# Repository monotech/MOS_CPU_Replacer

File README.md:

# Monotech PCs - MOS CPU Replacer  
**Replace rare/expensive/unreliable MOS CPUs**  
6510 *(C64) (8500 is same as 6510)*  
6510T *(1551 floppy drive)*  
8501 *(C16, C116, Plus/4) (7501 is same as 8501)*  
8502 *(C128)*

Licensed under Creative Commons BY-SA: (https://creativecommons.org/licenses/by-sa/4.0/)

If you want one, check my store for stock: (https://monotech.fwscart.com)

The above four CPUs have the same dies I believe, with just different internal pads exposed to the DIP-40 pins.  
It's a standard 6502 die, with an added 8-bit bidirectional I/O port, tri-state bus buffers, and an AEC latch enable for 8501 mode.

This device uses a standard 6502 CPU, and implements the extra functions using discrete logic - no programmable parts.  
Standard 6502 CPUs are abundant and cheap, and produced by many manufacturers (Rockwell, UMC, Synertek, MOS, etc).

You can use a 65C02 or W65C02, but this is untested, and will cause compatibility issues with some software at the least, or not work at the worst.  
If using a WDC W65C02, you must cut jumper W.

Build instructions are on the back of the PCB. This document is for clarification if you find it unclear.

It may struggle to fit inside a C116 or Plus/4 due to height, so for these machines you should solder the 6502 directly to the module's PCB, or solder the module directly to the C116 or Plus/4 motherboard.  
For C16, height is not a problem.

It is tested to fit next to a PLA20V8 replacement in a 250407 board. Other oversized replacement boards may interfere and require installing the module in an extra socket to raise it up.

Status as of Rev1:
-

- :heavy_check_mark: 6510 config: Tested working in a C64 and C64C with a wide range of software. In one scenario, it was discovered that it causes graphical glitches when used in a C64 with a C0pperdragon video conversion device (which watches the VIC-II pins). This was on Rev1. It may or may not be resolved on Rev2.
- :heavy_check_mark: 6510T config: I don't have a 1551, but someone else has done some basic testing in their own, and it works.
- :x: 8501 config: Tested working in a C16 and a Plus/4, but it has been found that at least one program crashes on a 64K-modded C16, that doesn't crash with a real 8501.
- :x: 8502 config: Works but has graphical glitches, likely due to a timing issue, so should only be built if you plan to help me diagnose this. For 8502, you must install a 2MHz-rated CPU (such as 6502A).

Known issues:
-

- A local enthusiast has discovered that using this adapter in 8501 config in their 64K-modded C16, results in Slipstream (https://psytronik.itch.io/slipstream) hanging, and causing resets to stop working (need a power cycle). One other person has confirmed this, and confirmed it doesn't happen with a real 8501, so the issue is with the MOS CPU Replacer. I will look into possible causes and update this page if a solution is found. Testing the C64 version of Slipstream in a C64 works fine with either a real 6510 or the MOS CPU Replacer in 6510 config.
- One user reported that it causes graphical glitches when used in a C64 (6510 config) with a C0pperdragon video conversion device (which watches the VIC-II pins), but works well otherwise. This was on Rev1. It may or may not be resolved on Rev2.
- I am sometimes working on improving the device, and hopefully reaching 100% compatibility.

---

Instructions:
-

1. Solder the solder-jumpers first (red dots).
1. Solder two 20-pin round-pin headers (cyan rectangles). (Not 21-pin!)
1. Solder the DIP-40 socket (yellow rectangles).
1. Install the 6502, and test the device.
    Don't install the device backwards or misaligned!

**The example picture below is for 8501 config (Jumpers: C, Headers: E). Steps 1 and 2 are different for the other three configs.**

**Troubleshooting**

- See the Known Issues section above.
- Double-check for shorts and that you soldered the correct solder jumpers.
- Crappy single-wipe IC sockets that Commodore used, can cause a lot of headache. Replace them.
- Your 6502 from Aliexpress/eBay may be fake or faulty. Sometimes they are actually 65C02 that have been re-marked as 6502.
- Some models of 6502 may be incompatible - I haven't tested all of them.
- I haven't tested every combination of Commodore motherboard revision, PLA replacement, marginal IC, or timing-sensitive demo.

**Changelog**

- Rev 2: used an unused HCT126 gate to buffer the PHI2 output, improving compatibility. Only affects 6510 and 6510T configurations which actually have a PHI2 output.
- Rev 1: First version

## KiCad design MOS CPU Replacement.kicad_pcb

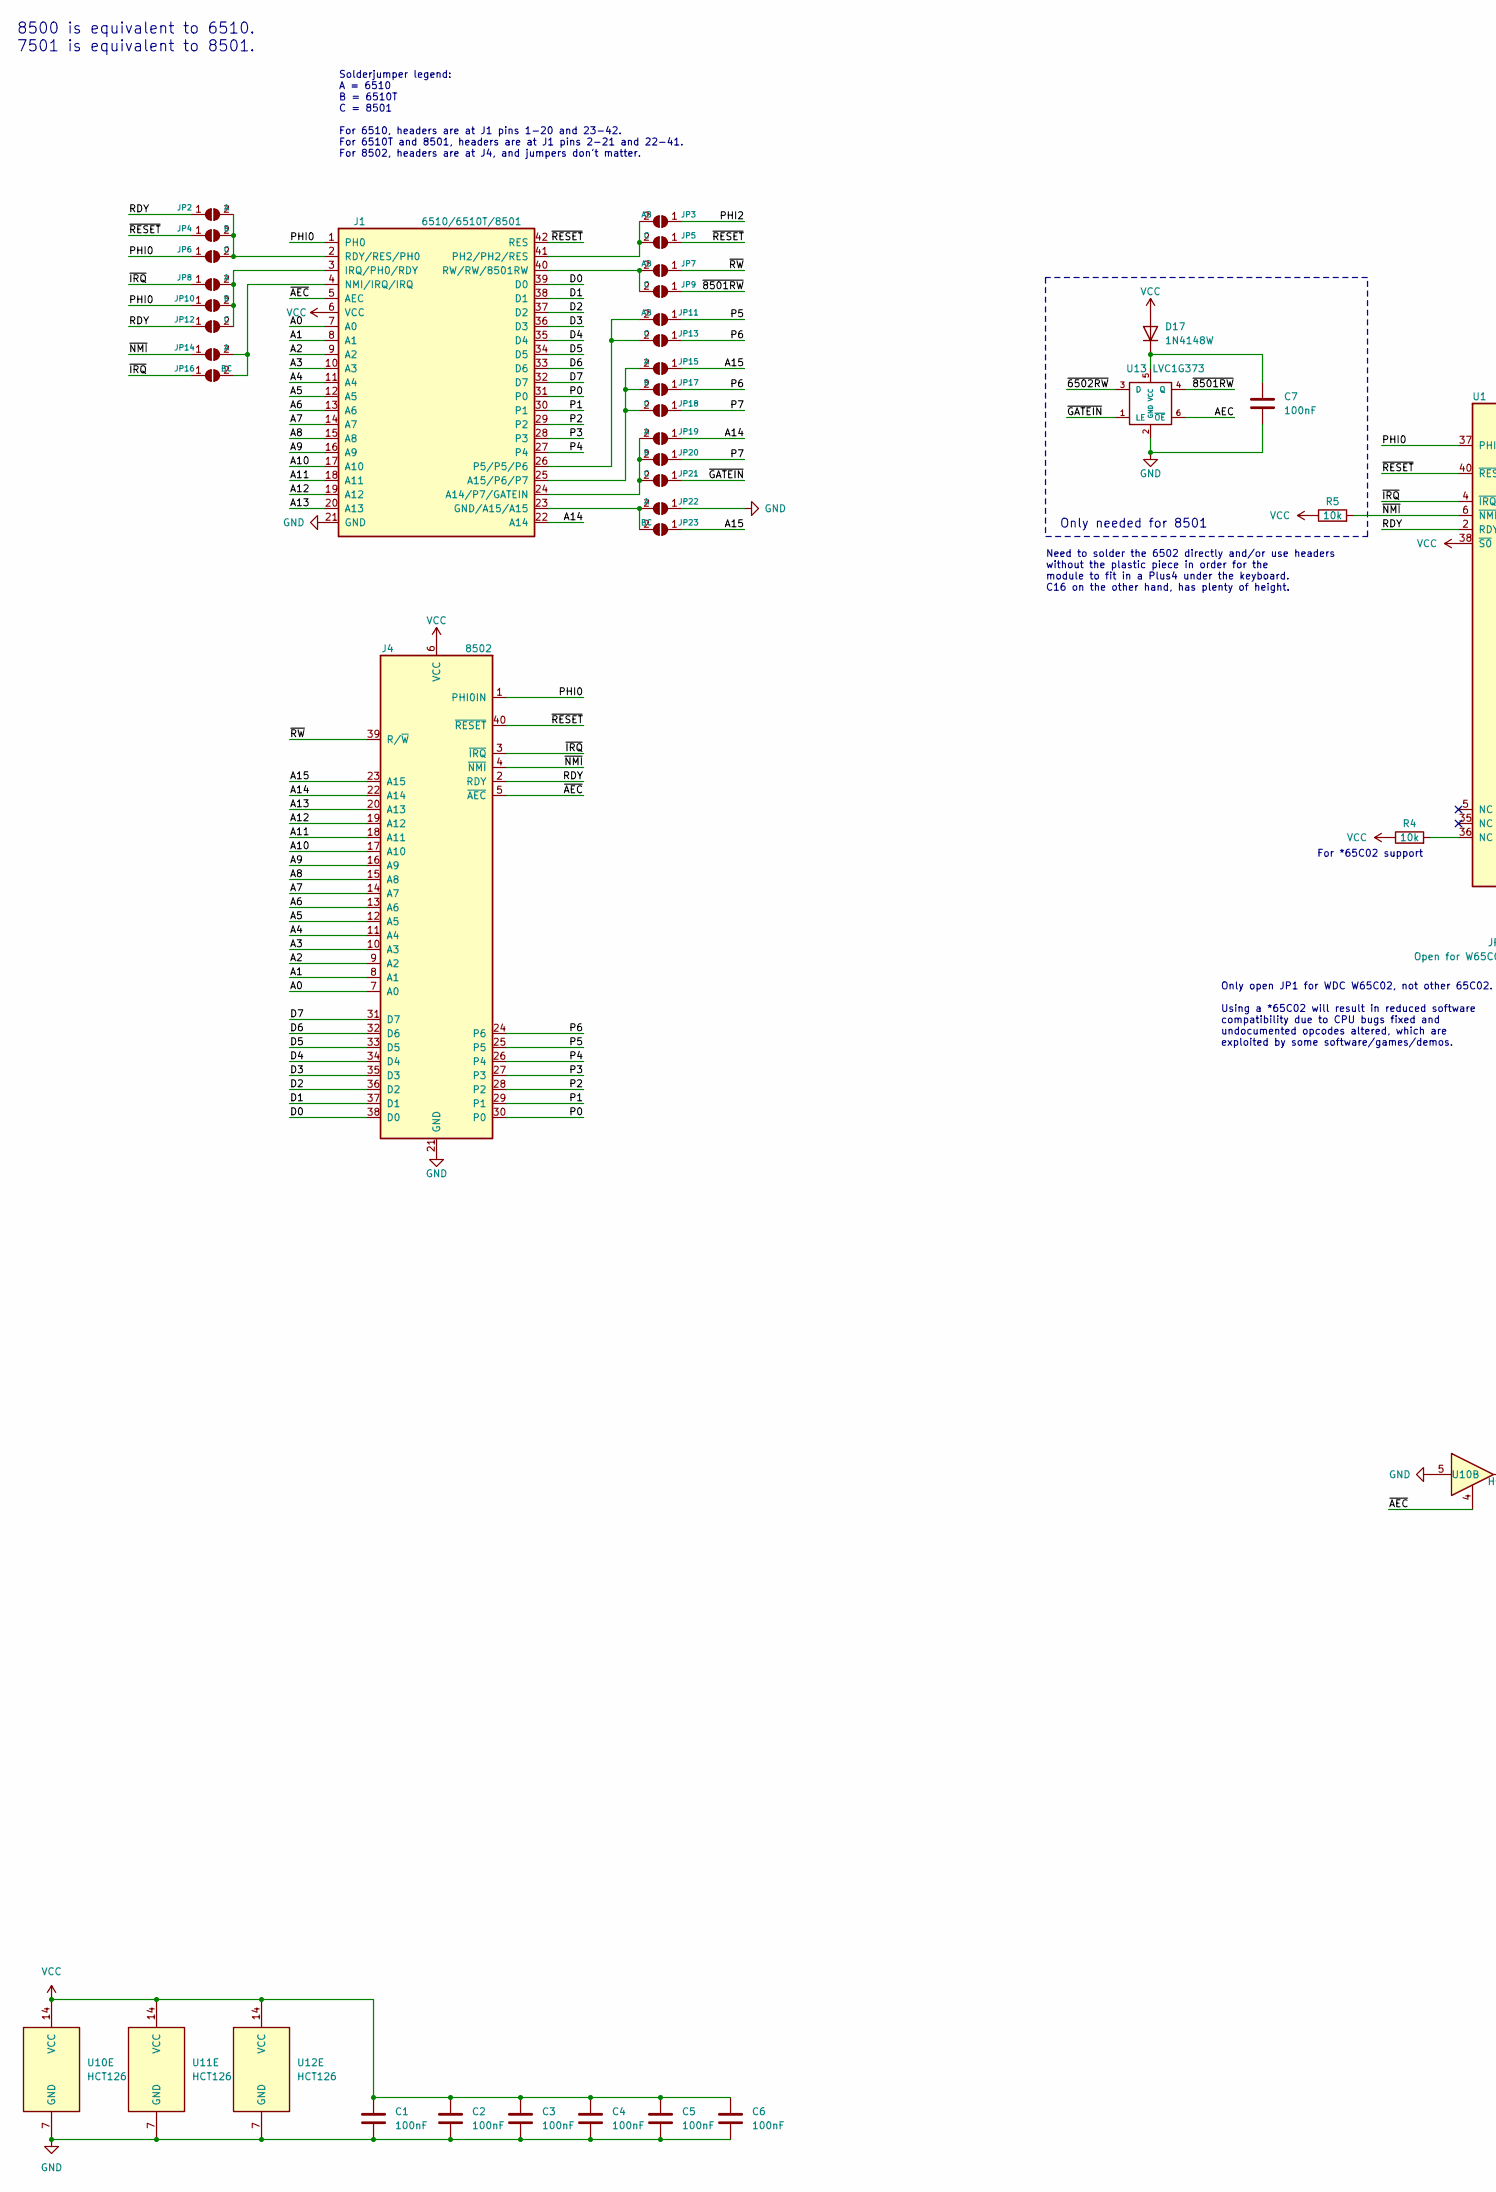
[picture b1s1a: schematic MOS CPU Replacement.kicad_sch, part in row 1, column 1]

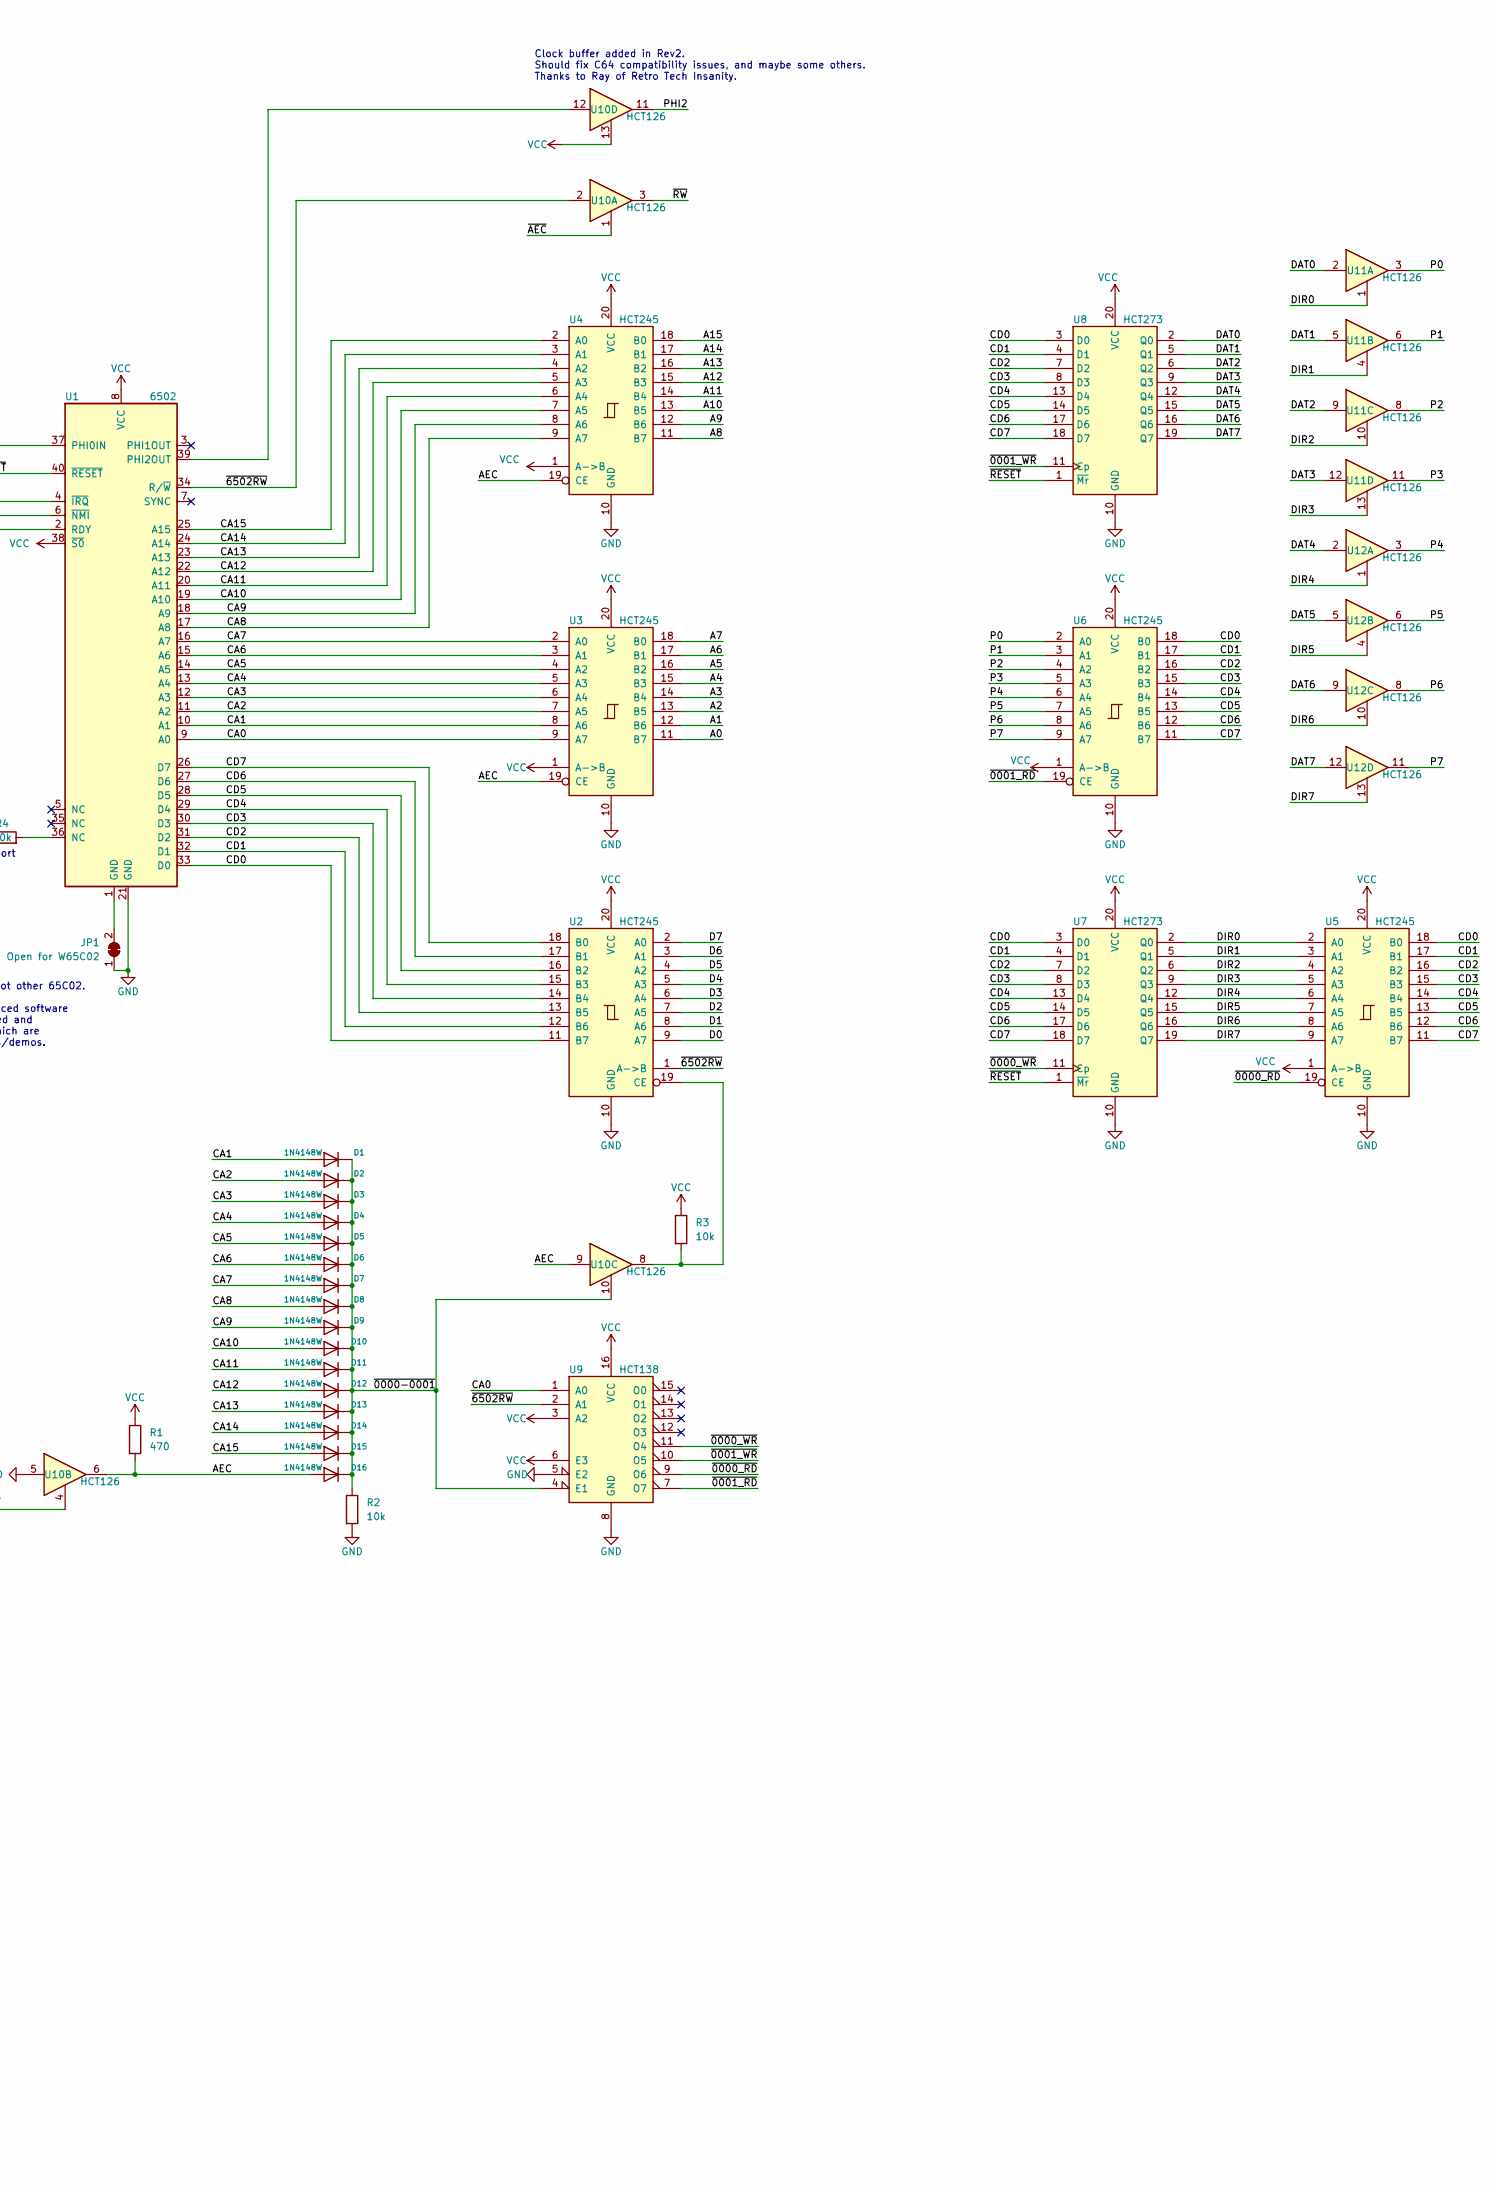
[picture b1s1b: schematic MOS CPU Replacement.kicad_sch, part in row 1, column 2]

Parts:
C1, C2, C3, C4, C5, C6, C7: 100nF; C_0402_1005Metric
D1, D2, D3, D4, D5, D6, D7, D8, D9, D10, D11, D12, D13, D14, D15, D16, D17: 1N4148W; D_SOD-323
J1: 6510/6510T/8501; 6510_6510T_8501_Socket
J4: 8502; DIP-40_W15.24mm_Socket
JP1: Open for W65C02; SolderJumper-2_P1.3mm_Bridged_RoundedPad1.0x1.5mm
JP2, JP8, JP14, JP15, JP19, JP22: A; SolderJumper-2_P1.3mm_Open_RoundedPad1.0x1.5mm
JP3, JP7, JP11: AB; SolderJumper-2_P1.3mm_Open_RoundedPad1.0x1.5mm
JP4, JP10, JP17, JP20: B; SolderJumper-2_P1.3mm_Open_RoundedPad1.0x1.5mm
JP5, JP6, JP9, JP12, JP13, JP18, JP21: C; SolderJumper-2_P1.3mm_Open_RoundedPad1.0x1.5mm
JP16, JP23: BC; SolderJumper-2_P1.3mm_Open_RoundedPad1.0x1.5mm
R1: 470; R_0805_2012Metric
R2, R3, R4, R5: 10k; R_0603_1608Metric
U1: 6502; DIP-40_W15.24mm_Socket
U2, U3, U4, U5, U6: HCT245; TSSOP-20_4.4x6.5mm_P0.65mm
U7, U8: HCT273; TSSOP-20_4.4x6.5mm_P0.65mm
U9: HCT138; TSSOP-16_4.4x5mm_P0.65mm
U10, U11, U12: HCT126; TSSOP-14_4.4x5mm_P0.65mm
U13: LVC1G373; SOT-363_SC-70-6

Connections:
/A0: J1.7 (A0), J4.7 (A0), U3.11 (B7)
/A1: J1.8 (A1), J4.8 (A1), U3.12 (B6)
/A2: J1.9 (A2), J4.9 (A2), U3.13 (B5)
/A3: J1.10 (A3), J4.10 (A3), U3.14 (B4)
/A4: J1.11 (A4), J4.11 (A4), U3.15 (B3)
/A5: J1.12 (A5), J4.12 (A5), U3.16 (B2)
/A6: J1.13 (A6), J4.13 (A6), U3.17 (B1)
/A7: J1.14 (A7), J4.14 (A7), U3.18 (B0)
/A8: J1.15 (A8), J4.15 (A8), U4.11 (B7)
/A9: J1.16 (A9), J4.16 (A9), U4.12 (B6)
/A10: J1.17 (A10), J4.17 (A10), U4.13 (B5)
/A11: J1.18 (A11), J4.18 (A11), U4.14 (B4)
/A12: J1.19 (A12), J4.19 (A12), U4.15 (B3)
/A13: J1.20 (A13), J4.20 (A13), U4.16 (B2)
/A14: J1.22 (A14), J4.22 (A14), JP19.1 (A), U4.17 (B1)
/A15: J4.23 (A15), JP15.1 (A), JP23.1 (A), U4.18 (B0)
/AEC: D16.2 (A), R1.2, U3.19 (CE), U4.19 (CE), U10.6, U10.9, U13.6 (~OE)
/CA0: U1.9 (A0), U3.9 (A7), U9.1 (A0)
/CA1: D1.2 (A), U1.10 (A1), U3.8 (A6)
/CA2: D2.2 (A), U1.11 (A2), U3.7 (A5)
/CA3: D3.2 (A), U1.12 (A3), U3.6 (A4)
/CA4: D4.2 (A), U1.13 (A4), U3.5 (A3)
/CA5: D5.2 (A), U1.14 (A5), U3.4 (A2)
/CA6: D6.2 (A), U1.15 (A6), U3.3 (A1)
/CA7: D7.2 (A), U1.16 (A7), U3.2 (A0)
/CA8: D8.2 (A), U1.17 (A8), U4.9 (A7)
/CA9: D9.2 (A), U1.18 (A9), U4.8 (A6)
/CA10: D10.2 (A), U1.19 (A10), U4.7 (A5)
/CA11: D11.2 (A), U1.20 (A11), U4.6 (A4)
/CA12: D12.2 (A), U1.22 (A12), U4.5 (A3)
/CA13: D13.2 (A), U1.23 (A13), U4.4 (A2)
/CA14: D14.2 (A), U1.24 (A14), U4.3 (A1)
/CA15: D15.2 (A), U1.25 (A15), U4.2 (A0)
/CD0: U1.33 (D0), U2.11 (B7), U5.18 (B0), U6.18 (B0), U7.3 (D0), U8.3 (D0)
/CD1: U1.32 (D1), U2.12 (B6), U5.17 (B1), U6.17 (B1), U7.4 (D1), U8.4 (D1)
/CD2: U1.31 (D2), U2.13 (B5), U5.16 (B2), U6.16 (B2), U7.7 (D2), U8.7 (D2)
/CD3: U1.30 (D3), U2.14 (B4), U5.15 (B3), U6.15 (B3), U7.8 (D3), U8.8 (D3)
/CD4: U1.29 (D4), U2.15 (B3), U5.14 (B4), U6.14 (B4), U7.13 (D4), U8.13 (D4)
/CD5: U1.28 (D5), U2.16 (B2), U5.13 (B5), U6.13 (B5), U7.14 (D5), U8.14 (D5)
/CD6: U1.27 (D6), U2.17 (B1), U5.12 (B6), U6.12 (B6), U7.17 (D6), U8.17 (D6)
/CD7: U1.26 (D7), U2.18 (B0), U5.11 (B7), U6.11 (B7), U7.18 (D7), U8.18 (D7)
/D0: J1.39 (D0), J4.38 (D0), U2.9 (A7)
/D1: J1.38 (D1), J4.37 (D1), U2.8 (A6)
/D2: J1.37 (D2), J4.36 (D2), U2.7 (A5)
/D3: J1.36 (D3), J4.35 (D3), U2.6 (A4)
/D4: J1.35 (D4), J4.34 (D4), U2.5 (A3)
/D5: J1.34 (D5), J4.33 (D5), U2.4 (A2)
/D6: J1.33 (D6), J4.32 (D6), U2.3 (A1)
/D7: J1.32 (D7), J4.31 (D7), U2.2 (A0)
/DAT0: U8.2 (Q0), U11.2
/DAT1: U8.5 (Q1), U11.5
/DAT2: U8.6 (Q2), U11.9
/DAT3: U8.9 (Q3), U11.12
/DAT4: U8.12 (Q4), U12.2
/DAT5: U8.15 (Q5), U12.5
/DAT6: U8.16 (Q6), U12.9
/DAT7: U8.19 (Q7), U12.12
/DIR0: U5.2 (A0), U7.2 (Q0), U11.1
/DIR1: U5.3 (A1), U7.5 (Q1), U11.4
/DIR2: U5.4 (A2), U7.6 (Q2), U11.10
/DIR3: U5.5 (A3), U7.9 (Q3), U11.13
/DIR4: U5.6 (A4), U7.12 (Q4), U12.1
/DIR5: U5.7 (A5), U7.15 (Q5), U12.4
/DIR6: U5.8 (A6), U7.16 (Q6), U12.10
/DIR7: U5.9 (A7), U7.19 (Q7), U12.13
/P0: J1.31 (P0), J4.30 (P0), U6.2 (A0), U11.3
/P1: J1.30 (P1), J4.29 (P1), U6.3 (A1), U11.6
/P2: J1.29 (P2), J4.28 (P2), U6.4 (A2), U11.8
/P3: J1.28 (P3), J4.27 (P3), U6.5 (A3), U11.11
/P4: J1.27 (P4), J4.26 (P4), U6.6 (A4), U12.3
/P5: J4.25 (P5), JP11.1 (A), U6.7 (A5), U12.6
/P6: J4.24 (P6), JP13.1 (A), JP17.1 (A), U6.8 (A6), U12.8
/P7: JP18.1 (A), JP20.1 (A), U6.9 (A7), U12.11
/PHI0: J1.1 (PH0), J4.1 (PHI0IN), JP6.1 (A), JP10.1 (A), U1.37 (PHI0IN)
/PHI2: JP3.1 (A), U10.11
/RDY: J4.2 (RDY), JP2.1 (A), JP12.1 (A), U1.2 (RDY)
/~0000-0001: D1.1 (K), D2.1 (K), D3.1 (K), D4.1 (K), D5.1 (K), D6.1 (K), D7.1 (K), D8.1 (K), D9.1 (K), D10.1 (K), D11.1 (K), D12.1 (K), D13.1 (K), D14.1 (K), D15.1 (K), D16.1 (K), R2.1, U9.4 (E1), U10.10
/~0000_RD: U5.19 (CE), U9.9 (O6)
/~0000_WR: U7.11 (Cp), U9.11 (O4)
/~0001_RD: U6.19 (CE), U9.7 (O7)
/~0001_WR: U8.11 (Cp), U9.10 (O5)
/~6502RW: U1.34 (R/~W), U2.1 (A->B), U9.2 (A1), U10.2, U13.3 (D)
/~8501RW: JP9.1 (A), U13.4 (Q)
/~AEC: J1.5 (AEC), J4.5 (~AEC), U10.1, U10.4
/~GATEIN: JP21.1 (A), U13.1 (LE)
/~IRQ: J4.3 (~IRQ), JP8.1 (A), JP16.1 (A), U1.4 (~IRQ)
/~NMI: J4.4 (~NMI), JP14.1 (A), R5.2, U1.6 (~NMI)
/~RESET: J1.42 (RES), J4.40 (~RESET), JP4.1 (A), JP5.1 (A), U1.40 (~RESET), U7.1 (~Mr), U8.1 (~Mr)
/~RW: J4.39 (R/~W), JP7.1 (A), U10.3
GND: C1.2, C2.2, C3.2, C4.2, C5.2, C6.2, C7.2, J1.21 (GND), J4.21 (GND), JP1.1 (A), JP22.1 (A), R2.2, U1.21 (GND), U2.10 (GND), U3.10 (GND), U4.10 (GND), U5.10 (GND), U6.10 (GND), U7.10 (GND), U8.10 (GND), U9.5 (E2), U9.8 (GND), U10.5, U10.7 (GND), U11.7 (GND), U12.7 (GND), U13.2 (GND)
unnamed: C7.1, D17.1 (K), U13.5 (VCC)
unnamed: J1.2 (RDY/RES/PH0), JP2.2 (B), JP4.2 (B), JP6.2 (B)
unnamed: J1.3 (IRQ/PH0/RDY), JP8.2 (B), JP10.2 (B), JP12.2 (B)
unnamed: J1.4 (NMI/IRQ/IRQ), JP14.2 (B), JP16.2 (B)
unnamed: J1.23 (GND/A15/A15), JP22.2 (B), JP23.2 (B)
unnamed: J1.24 (A14/P7/GATEIN), JP19.2 (B), JP20.2 (B), JP21.2 (B)
unnamed: J1.25 (A15/P6/P7), JP15.2 (B), JP17.2 (B), JP18.2 (B)
unnamed: J1.26 (P5/P5/P6), JP11.2 (B), JP13.2 (B)
unnamed: J1.40 (RW/RW/8501RW), JP7.2 (B), JP9.2 (B)
unnamed: J1.41 (PH2/PH2/RES), JP3.2 (B), JP5.2 (B)
unnamed: JP1.2 (B), U1.1 (GND)
unnamed: R3.2, U2.19 (CE), U10.8
unnamed: R4.2, U1.36 (NC)
unnamed: U1.39 (PHI2OUT), U10.12
VCC: C1.1, C2.1, C3.1, C4.1, C5.1, C6.1, D17.2 (A), J1.6 (VCC), J4.6 (VCC), R1.1, R3.1, R4.1, R5.1, U1.8 (VCC), U1.38 (~S0), U2.20 (VCC), U3.1 (A->B), U3.20 (VCC), U4.1 (A->B), U4.20 (VCC), U5.1 (A->B), U5.20 (VCC), U6.1 (A->B), U6.20 (VCC), U7.20 (VCC), U8.20 (VCC), U9.3 (A2), U9.6 (E3), U9.16 (VCC), U10.13, U10.14 (VCC), U11.14 (VCC), U12.14 (VCC)

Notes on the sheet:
Only needed for 8501
Need to solder the 6502 directly and/or use headers without the plastic piece in order for the module to fit in a Plus4 under the keyboard. C16 on the other hand, has plenty of height.
8500 is equivalent to 6510. 7501 is equivalent to 8501.
Only open JP1 for WDC W65C02, not other 65C02. Using a *65C02 will result in reduced software compatibility due to CPU bugs fixed and undocumented opcodes altered, which are exploited by some software/games/demos.
Clock buffer added in Rev2. Should fix C64 compatibility issues, and maybe some others. Thanks to Ray of Retro Tech Insanity.
For *65C02 support
Solderjumper legend: A = 6510 B = 6510T C = 8501 For 6510, headers are at J1 pins 1-20 and 23-42. For 6510T and 8501, headers are at J1 pins 2-21 and 22-41. For 8502, headers are at J4, and jumpers don't matter.

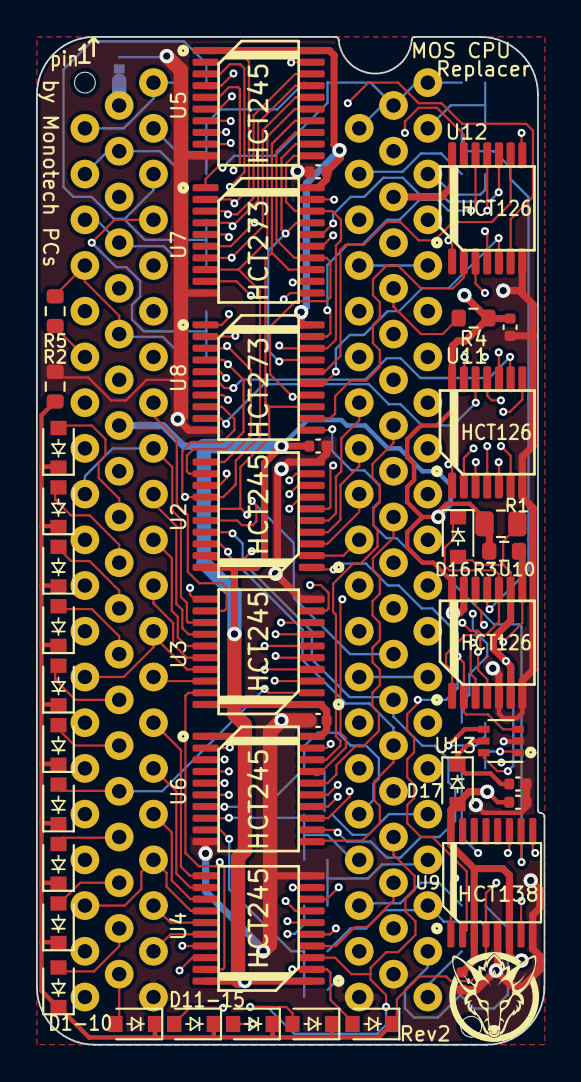
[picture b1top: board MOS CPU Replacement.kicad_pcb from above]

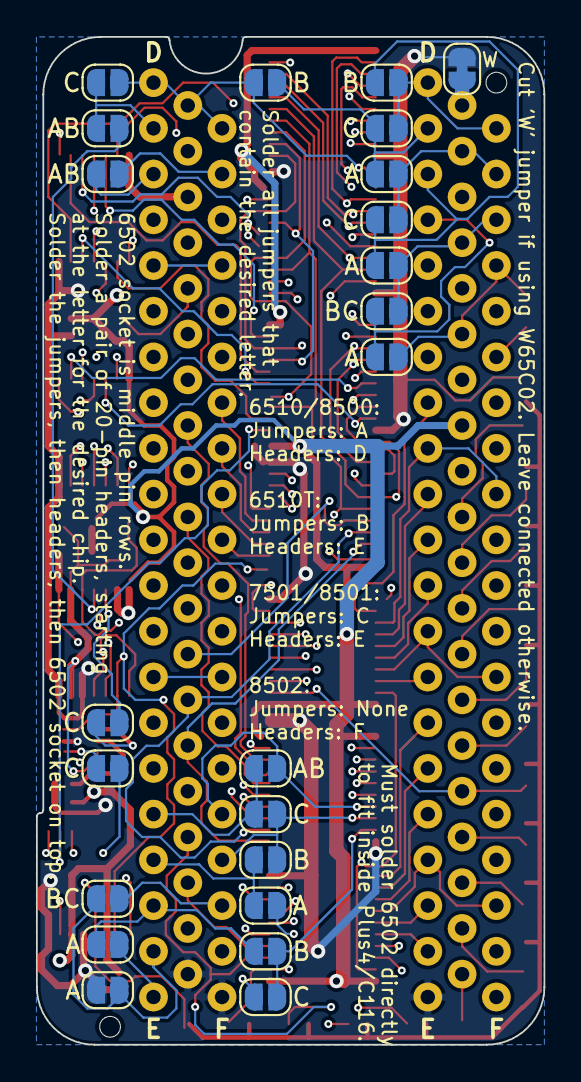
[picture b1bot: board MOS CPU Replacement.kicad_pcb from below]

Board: 4 copper layers, 28.2 x 56.0 mm, 68 parts (23 on the bottom side), 105 nets.

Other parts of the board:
LOGO1: LOGO

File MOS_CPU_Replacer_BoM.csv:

Qty,Reference,Part model,Footprint,Mouser part number,Digikey part number,Notes
7,C1-7,100nF,402,187-CL05B104KP5NNWC,1276-1510-1-ND,C7 only needed for 8501
17,D1-17,1N4148W,SOD-323,241-1N4148WSR100001,1655-1359-1-ND,D17 only needed for 8501
1,R1,470,805,603-RC0805JR-07470RP,A130132CT-ND,
4,R2-5,10k,603,603-RC0603FR-1310KL,311-10KGRCT-ND,R4 only needed for *65C02 support
5,U2-6,74HCT245,TSSOP-20,595-SN74HCT245PWR,296-8404-1-ND,
2,U7-8,74HCT273,TSSOP-20,595-SN74HCT273PWR,296-8409-1-ND,
1,U9,74HCT138,TSSOP-16,771-HCT138PW118,1727-2050-1-ND,
3,U10-12,74HCT126,TSSOP-14,771-HCT126PW118,1727-6619-1-ND,
1,U13,74LVC1G373,SOT-363,595-74LVC1G373DCKRG4,296-18775-1-ND,U13 only needed for 8501
1,,40-pin round-pin header,,872-920-0172-01,1988-1163-ND,Cut it in half
1,,DIP-40 round-pin socket,DIP-40,575-11044640,ED3033-ND,
1,,6502 CPU,DIP-40,N/A,,

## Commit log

2023-05-04 Update to Rev2

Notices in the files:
MOS CPU Replacement.kicad_sch:
License: Creative Commons BY-SA
